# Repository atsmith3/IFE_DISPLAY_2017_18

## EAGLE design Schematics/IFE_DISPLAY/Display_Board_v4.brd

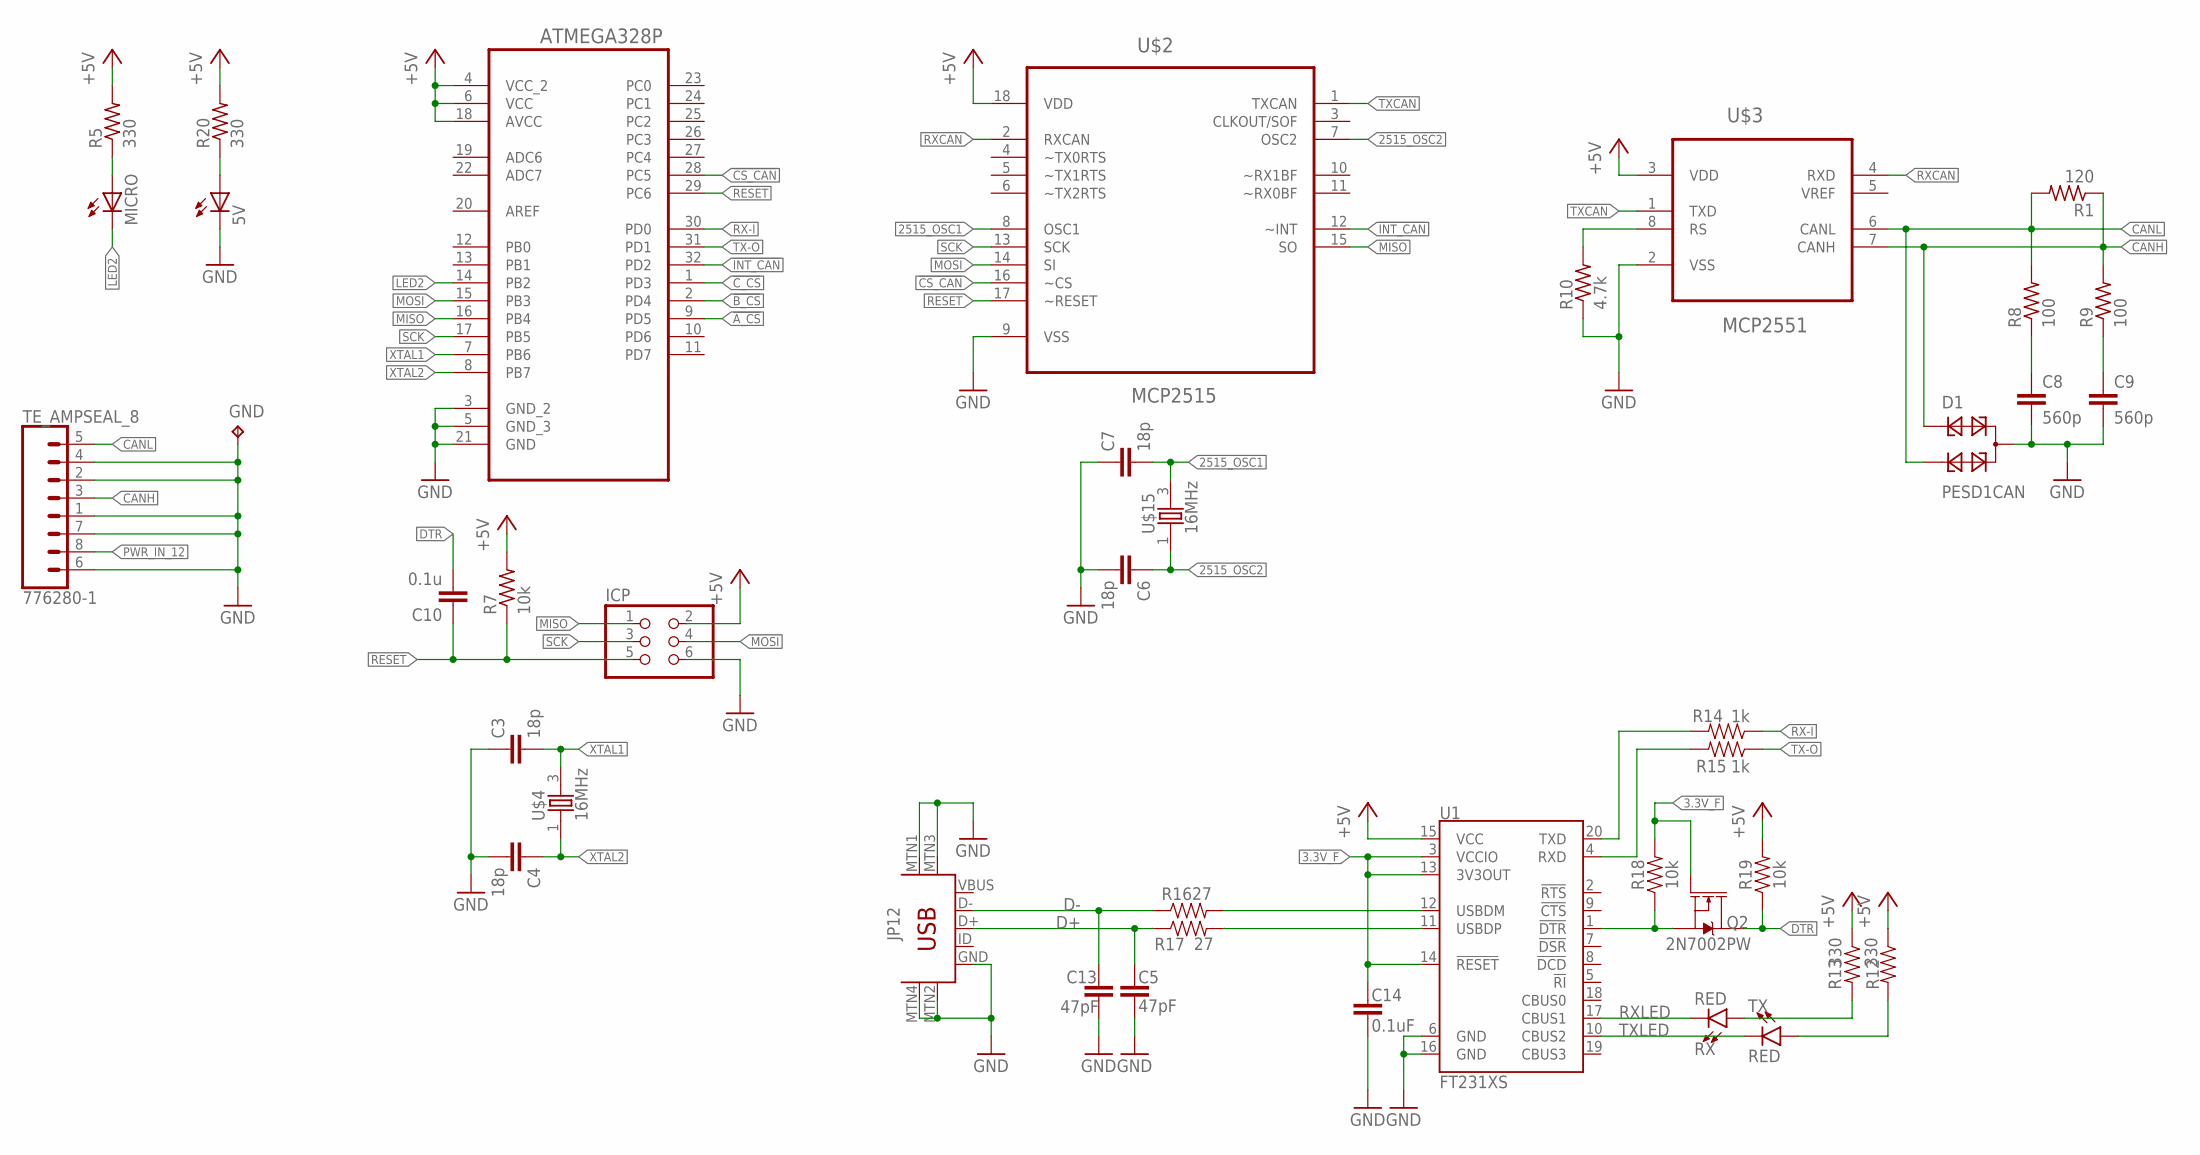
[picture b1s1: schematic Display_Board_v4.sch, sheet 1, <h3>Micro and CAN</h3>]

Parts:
5V: LEDCHIP-LED0805; CHIP-LED0805
ATMEGA328P: ATMEGA328P-AU; QFP80P900X900X120-32N
C3, C4, C6, C7: 18p; C0805K
C5, C13: 47pF; 0603
C8, C9: 560p; C0805K
C10: 0.1u; C0805K
C14: 0.1uF; 0603
D1: PESD1CAN; SOT23
GND: TPTP12SQ; TP12SQ
ICP: PINHD-2X3; 2X03
JP12: USB-MINIB-5PIN; USB-MINIB
MICRO: LEDCHIP-LED0805; CHIP-LED0805
Q2: 2N7002PW; SOT323
R1: 120; R0805
R5, R20: 330; R0805
R7: 10k; R0805
R8, R9: 100; R0805
R10: 4.7k; R0805
R12, R13: 330; 0603
R14, R15: 1k; 0603
R16, R17: 27; 0603
R18, R19: 10k; 0603
RX: RED; LED-1206
TE_AMPSEAL_8: 776280-1
TX: RED; LED-1206
U1: FT231XS; SSOP20_L
U$2: MCP2515; SOIC127P1034X264-18N
U$3: MCP2551; SOIC127P600X175-8N
U$4, U$15: 16MHz; CTS406

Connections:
3.3V_F: C14.1, Q2.1 (G), R18.2, U1.3 (VCCIO), U1.13 (3V3OUT), U1.14 (!RESET)
2515_OSC1: C7.2, U$2.8 (OSC1), U$15.3 (2)
2515_OSC2: C6.1, U$2.7 (OSC2), U$15.1
!A_CS: ATMEGA328P.9 (PD5); also elsewhere on the board
!B_CS: ATMEGA328P.2 (PD4); also elsewhere on the board
!CS_CAN: ATMEGA328P.28 (PC5), U$2.16 (~CS)
!C_CS: ATMEGA328P.1 (PD3); also elsewhere on the board
!INT_CAN: ATMEGA328P.32 (PD2), U$2.12 (~INT)
+5V: ATMEGA328P.4 (VCC_2), ATMEGA328P.6 (VCC), ATMEGA328P.18 (AVCC), ICP.2, R5.2, R7.2, R12.1, R13.1, R19.2, R20.2, U1.15 (VCC), U$2.18 (VDD), U$3.3 (VDD); also elsewhere on the board
CANH: D1.1, R1.1, R9.2, TE_AMPSEAL_8.3 (5), U$3.7 (CANH)
CANL: D1.2, R1.2, R8.2, TE_AMPSEAL_8.5 (8), U$3.6 (CANL)
D+: C5.1, JP12.D+, R17.1
D-: C13.1, JP12.D-, R16.1
DTR: C10.2, Q2.3 (D), R19.1
FTDI_DTR: Q2.2 (S), R18.1, U1.1 (!DTR)
GND: 5V.C, ATMEGA328P.3 (GND_2), ATMEGA328P.5 (GND_3), ATMEGA328P.21 (GND), C3.1, C4.2, C5.2, C6.2, C7.1, C8.2, C9.2, C13.2, C14.2, D1.3, GND.TP, ICP.6, JP12.GND, JP12.MTN1 (MTN2), JP12.MTN2 (MTN3), JP12.MTN3 (MTN1), JP12.MTN4, R10.1, TE_AMPSEAL_8.1 (4), TE_AMPSEAL_8.2 (6), TE_AMPSEAL_8.4 (7), TE_AMPSEAL_8.6 (1), TE_AMPSEAL_8.7 (3), U1.6 (GND), U1.16 (GND), U$2.9 (VSS), U$3.2 (VSS); also elsewhere on the board
LED2: ATMEGA328P.14 (PB2), MICRO.C
MISO: ATMEGA328P.16 (PB4), ICP.1, U$2.15 (SO); also elsewhere on the board
MOSI: ATMEGA328P.15 (PB3), ICP.4, U$2.14 (SI); also elsewhere on the board
unnamed: R12.2, TX.A
unnamed: R16.2, U1.12 (USBDM)
unnamed: MICRO.A, R5.1
unnamed: R17.2, U1.11 (USBDP)
unnamed: R10.2, U$3.8 (RS)
unnamed: C8.1, R8.1
unnamed: C9.1, R9.1
unnamed: R13.2, RX.A
unnamed: 5V.A, R20.1
PWR_IN_12: TE_AMPSEAL_8.8 (2); also elsewhere on the board
RESET: ATMEGA328P.29 (PC6), C10.1, ICP.5, R7.1, U$2.17 (~RESET)
RX-I: ATMEGA328P.30 (PD0), R14.1
RXCAN: U$2.2 (RXCAN), U$3.4 (RXD)
RXD1: R15.2, U1.4 (RXD)
RXLED: RX.C, U1.17 (CBUS1)
SCK: ATMEGA328P.17 (PB5), ICP.3, U$2.13 (SCK); also elsewhere on the board
TX-O: ATMEGA328P.31 (PD1), R15.1
TXCAN: U$2.1 (TXCAN), U$3.1 (TXD)
TXD1: R14.2, U1.20 (TXD)
TXLED: TX.C, U1.10 (CBUS2)
XTAL1: ATMEGA328P.7 (PB6), C3.2, U$4.3 (2)
XTAL2: ATMEGA328P.8 (PB7), C4.1, U$4.1

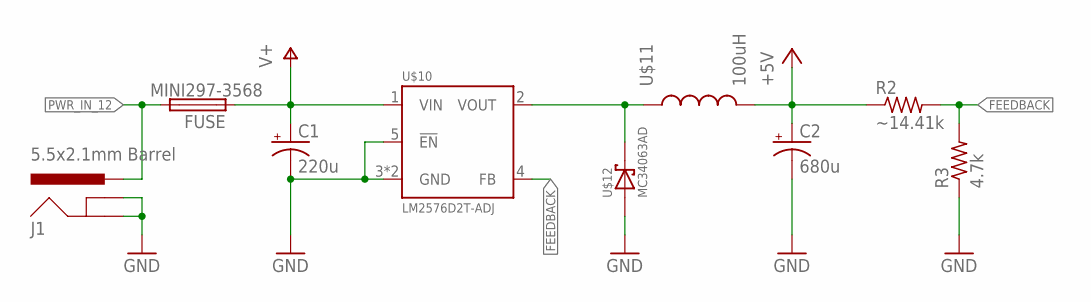
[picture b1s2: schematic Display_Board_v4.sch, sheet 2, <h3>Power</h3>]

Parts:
C1: 220u; UD-6,3X7,7_NICHICON
C2: 680u; UD-6,3X7,7_NICHICON
FUSE: MINI297-3568; 3568
J1: 5.5x2.1mm Barrel; POWER_JACK_SMD
R2: ~14.41k; R0603
R3: 4.7k; R0603
U$10: LM2576D2T-ADJ; TO263-5
U$11: 100uH; 12MM_12MM_INDUCTOR
U$12: MC34063AD; SMC

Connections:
+5V: C2.+, R2.1, U$11.P$2 (2); also elsewhere on the board
FEEDBACK: R2.2, R3.2, U$10.4 (FB)
GND: C1.-, C2.-, J1.GND (GNDBREAK), J1.P$4 (GND), R3.1, U$10.3 (GND), U$10.5 (!EN), U$10.6 (GND), U$12.A; also elsewhere on the board
unnamed: U$10.2 (VOUT), U$11.P$1 (1), U$12.C
PWR_IN_12: FUSE.P$2 (2), FUSE.P$3 (2), J1.VIN0 (PWR); also elsewhere on the board
V+: C1.+, FUSE.P$1 (1), FUSE.P$4 (1), U$10.1 (VIN)

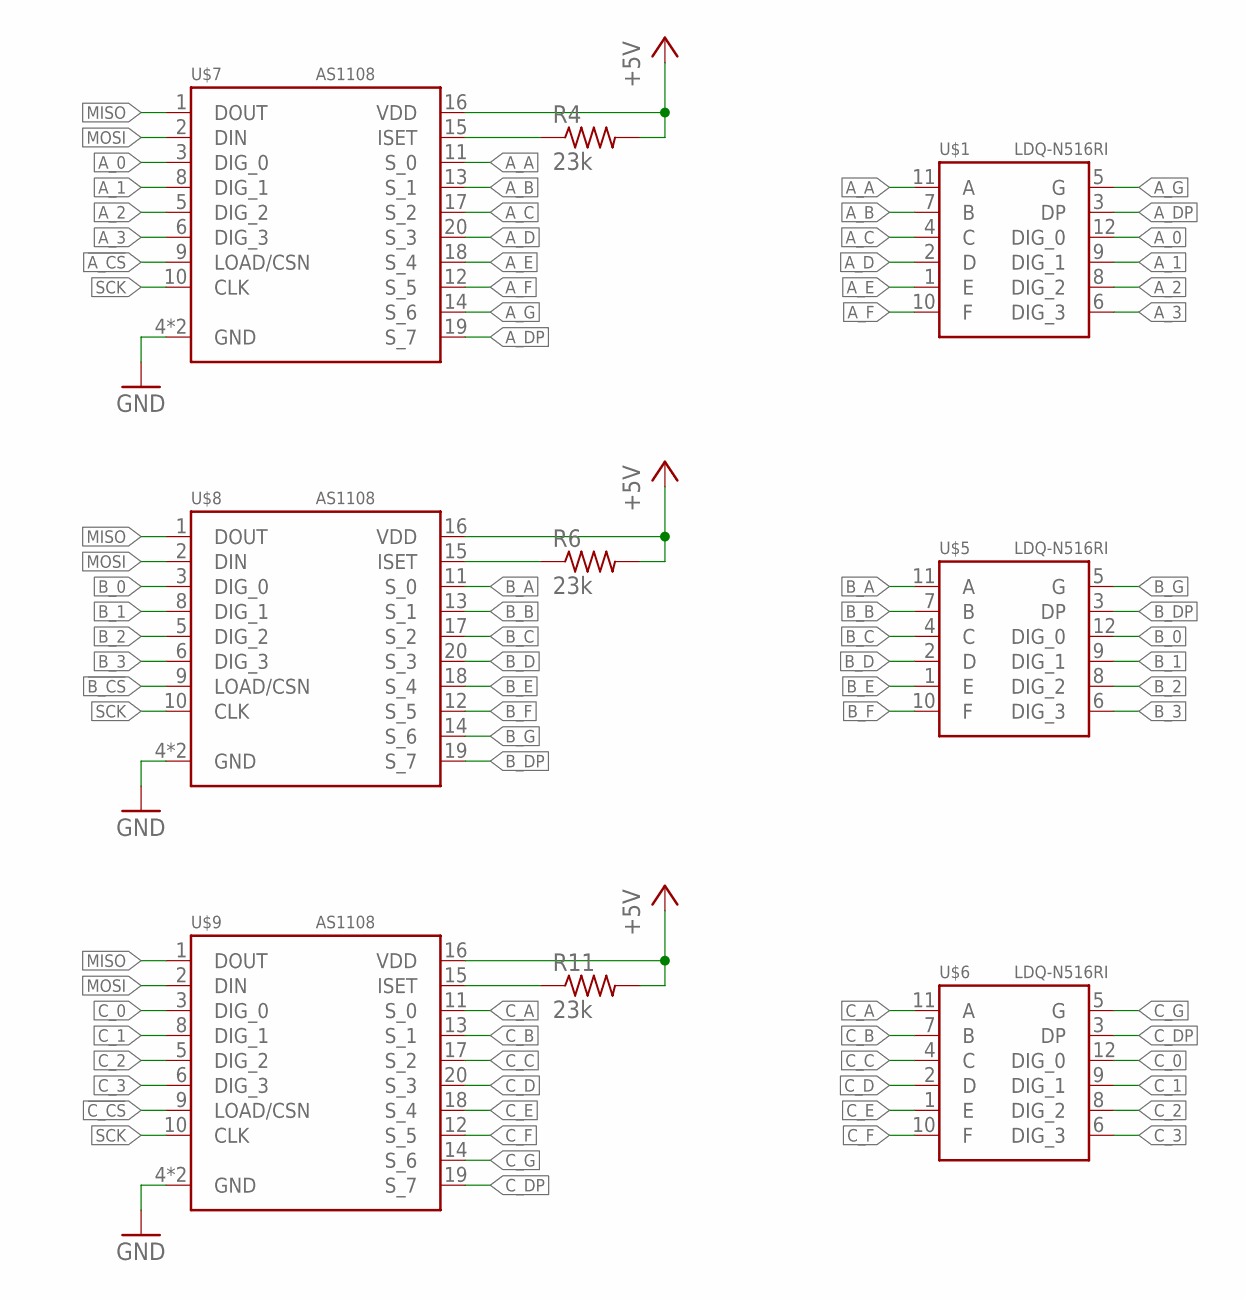
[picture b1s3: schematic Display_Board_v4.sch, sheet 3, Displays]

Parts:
R4, R6, R11: 23k; R0603
U$1, U$5, U$6: LDQ-N516RI; 4_DIGIT_7_SEGMENT_DISPLAY_0.56"
U$7, U$8, U$9: AS1108; SO20L

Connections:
!A_CS: U$7.9 (LOAD/CSN); also elsewhere on the board
!B_CS: U$8.9 (LOAD/CSN); also elsewhere on the board
!C_CS: U$9.9 (LOAD/CSN); also elsewhere on the board
+5V: R4.2, R6.2, R11.2, U$7.16 (VDD), U$8.16 (VDD), U$9.16 (VDD); also elsewhere on the board
A_0: U$1.12 (DIG_0), U$7.3 (DIG_0)
A_1: U$1.9 (DIG_1), U$7.8 (DIG_1)
A_2: U$1.8 (DIG_2), U$7.5 (DIG_2)
A_3: U$1.6 (DIG_3), U$7.6 (DIG_3)
A_A: U$1.11 (A), U$7.11 (S_0)
A_B: U$1.7 (B), U$7.13 (S_1)
A_C: U$1.4 (C), U$7.17 (S_2)
A_D: U$1.2 (D), U$7.20 (S_3)
A_DP: U$1.3 (DP), U$7.19 (S_7)
A_E: U$1.1 (E), U$7.18 (S_4)
A_F: U$1.10 (F), U$7.12 (S_5)
A_G: U$1.5 (G), U$7.14 (S_6)
B_0: U$5.12 (DIG_0), U$8.3 (DIG_0)
B_1: U$5.9 (DIG_1), U$8.8 (DIG_1)
B_2: U$5.8 (DIG_2), U$8.5 (DIG_2)
B_3: U$5.6 (DIG_3), U$8.6 (DIG_3)
B_A: U$5.11 (A), U$8.11 (S_0)
B_B: U$5.7 (B), U$8.13 (S_1)
B_C: U$5.4 (C), U$8.17 (S_2)
B_D: U$5.2 (D), U$8.20 (S_3)
B_DP: U$5.3 (DP), U$8.19 (S_7)
B_E: U$5.1 (E), U$8.18 (S_4)
B_F: U$5.10 (F), U$8.12 (S_5)
B_G: U$5.5 (G), U$8.14 (S_6)
C_0: U$6.12 (DIG_0), U$9.3 (DIG_0)
C_1: U$6.9 (DIG_1), U$9.8 (DIG_1)
C_2: U$6.8 (DIG_2), U$9.5 (DIG_2)
C_3: U$6.6 (DIG_3), U$9.6 (DIG_3)
C_A: U$6.11 (A), U$9.11 (S_0)
C_B: U$6.7 (B), U$9.13 (S_1)
C_C: U$6.4 (C), U$9.17 (S_2)
C_D: U$6.2 (D), U$9.20 (S_3)
C_DP: U$6.3 (DP), U$9.19 (S_7)
C_E: U$6.1 (E), U$9.18 (S_4)
C_F: U$6.10 (F), U$9.12 (S_5)
C_G: U$6.5 (G), U$9.14 (S_6)
GND: U$7.4 (GND), U$7.7 (GND), U$8.4 (GND), U$8.7 (GND), U$9.4 (GND), U$9.7 (GND); also elsewhere on the board
MISO: U$7.1 (DOUT), U$8.1 (DOUT), U$9.1 (DOUT); also elsewhere on the board
MOSI: U$7.2 (DIN), U$8.2 (DIN), U$9.2 (DIN); also elsewhere on the board
unnamed: R6.1, U$8.15 (ISET)
unnamed: R11.1, U$9.15 (ISET)
unnamed: R4.1, U$7.15 (ISET)
SCK: U$7.10 (CLK), U$8.10 (CLK), U$9.10 (CLK); also elsewhere on the board

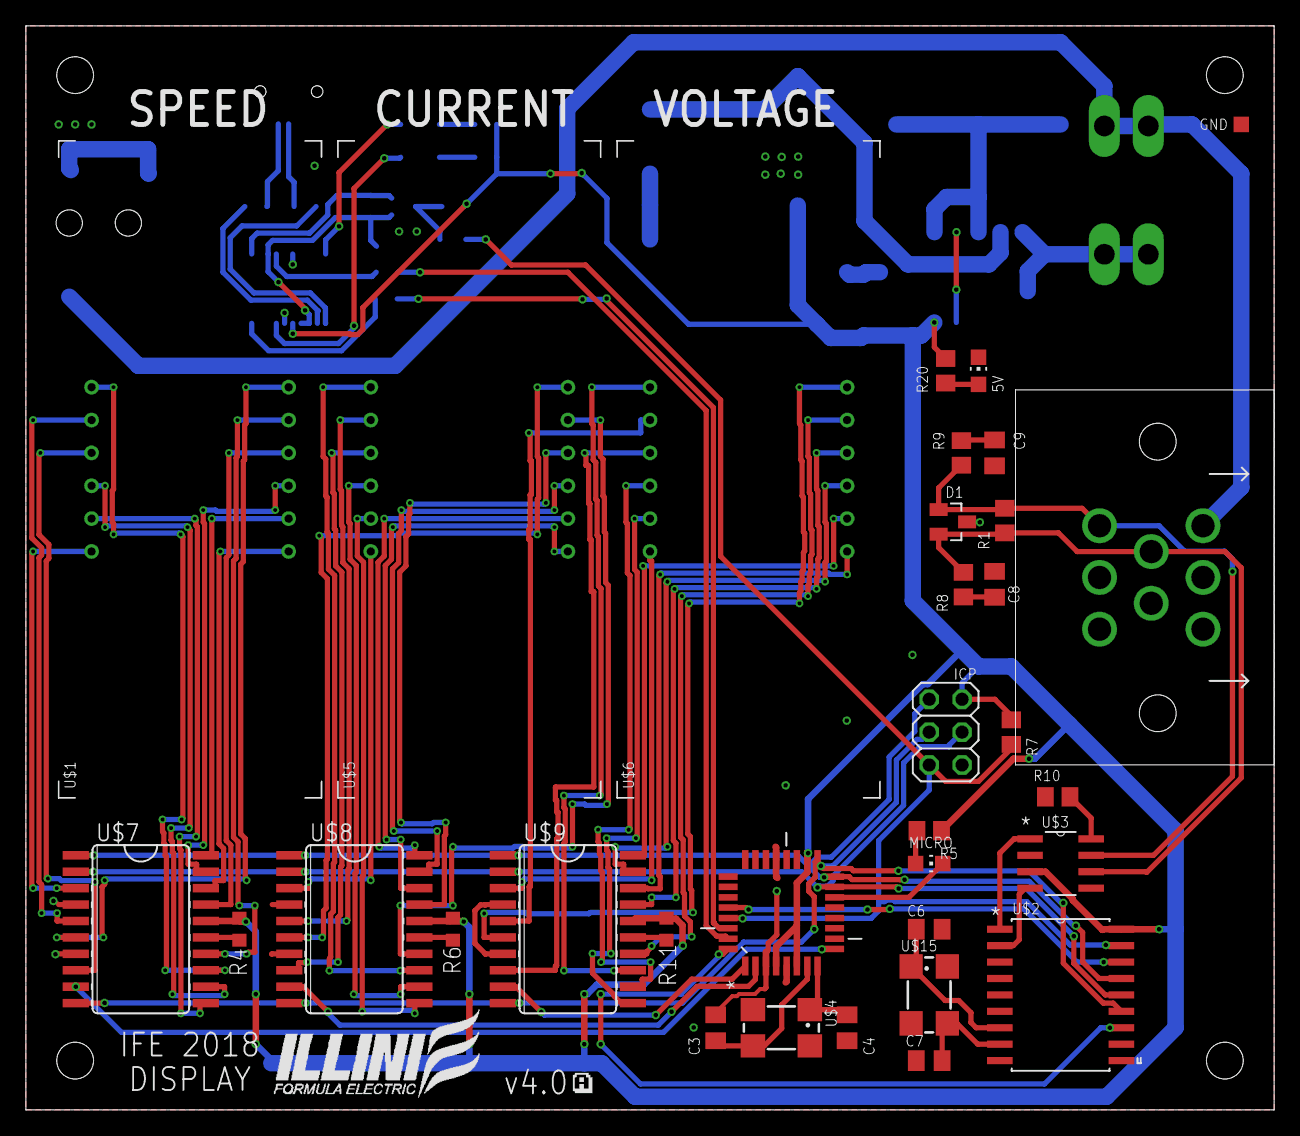
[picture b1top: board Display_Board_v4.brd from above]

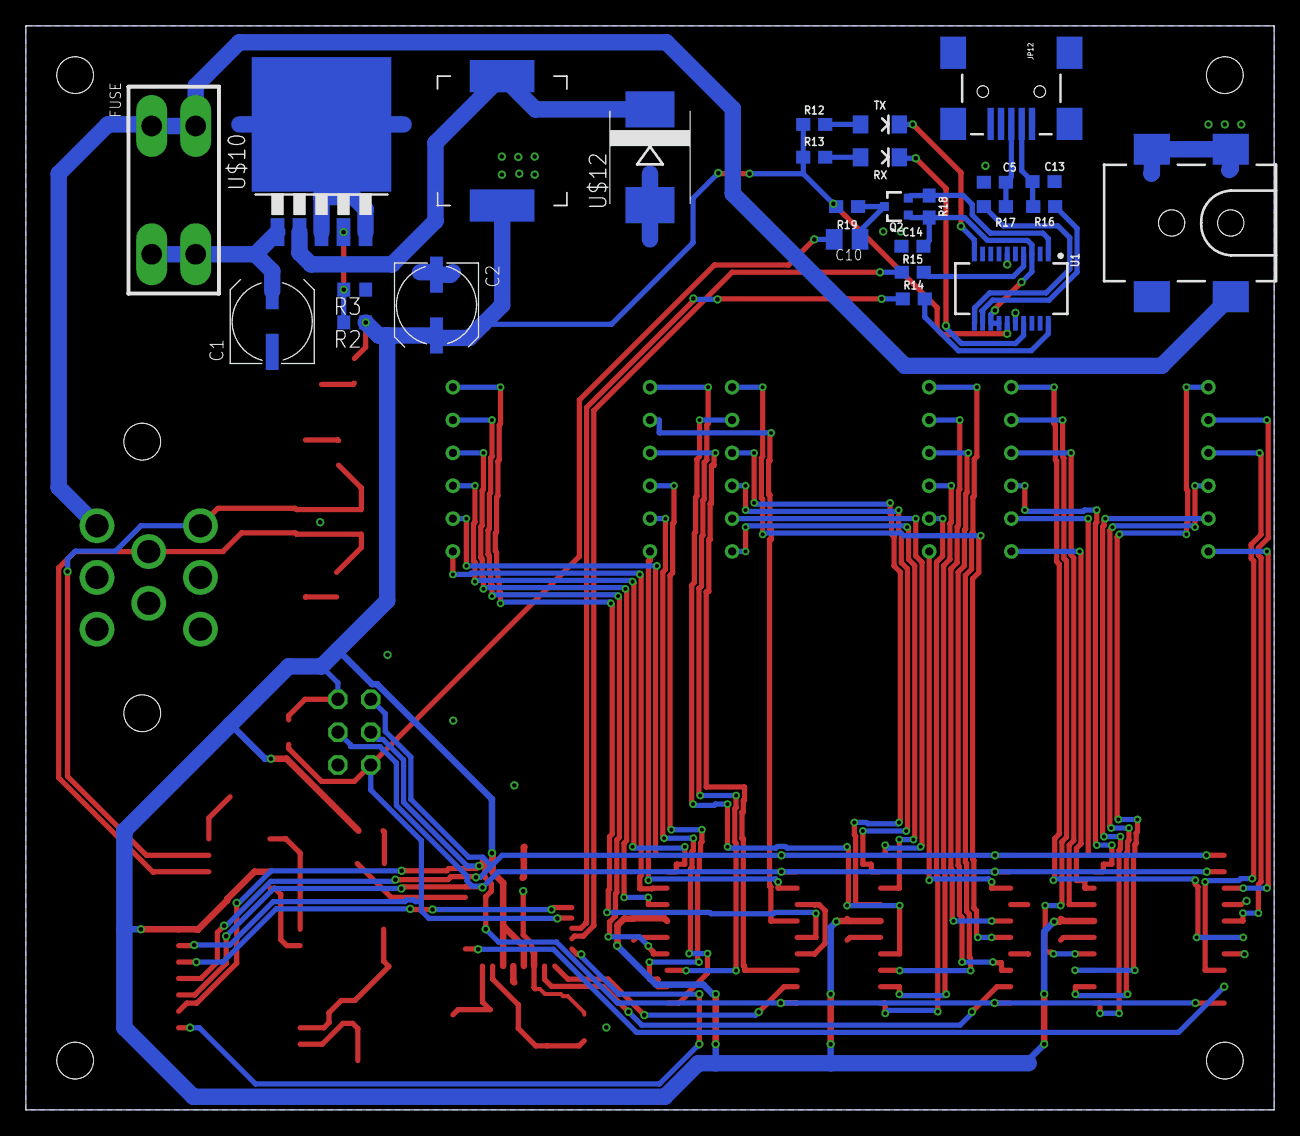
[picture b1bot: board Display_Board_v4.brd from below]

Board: 2 copper layers, 96.5 x 83.8 mm, 59 parts (26 on the bottom side), 83 nets.

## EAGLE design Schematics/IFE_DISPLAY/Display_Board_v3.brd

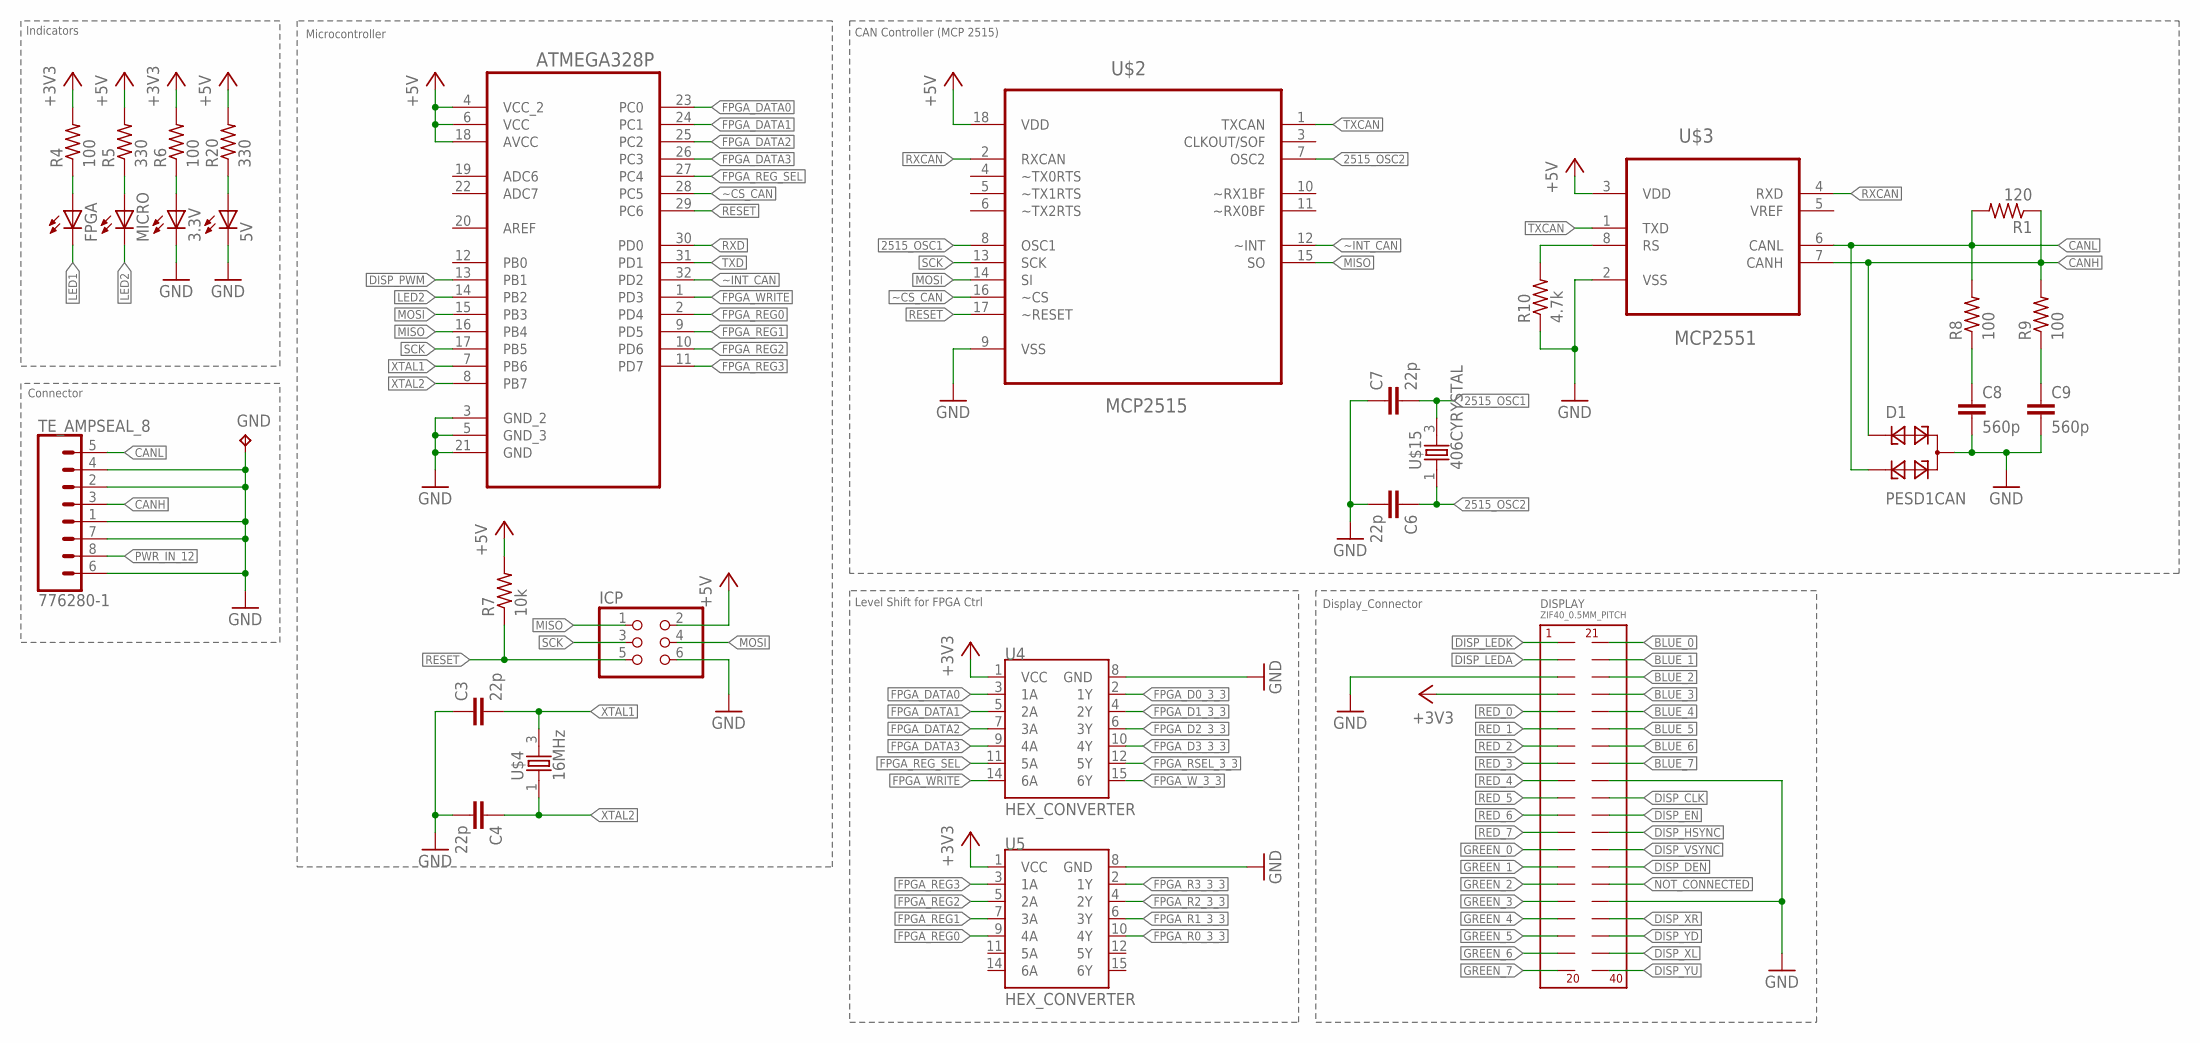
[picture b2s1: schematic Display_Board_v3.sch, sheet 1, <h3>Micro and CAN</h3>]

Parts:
3.3V, 5V: LEDCHIP-LED0805; CHIP-LED0805
ATMEGA328P: ATMEGA328P-AU; QFP80P900X900X120-32N
C3, C4, C6, C7: 22p; C0805K
C8, C9: 560p; C0805K
D1: PESD1CAN; SOT23
DISPLAY: ZIF40_0.5MM_PITCH; ZIF40
FPGA: LEDCHIP-LED0805; CHIP-LED0805
GND: TPTP12SQ; TP12SQ
ICP: PINHD-2X3; 2X03
MICRO: LEDCHIP-LED0805; CHIP-LED0805
R1: 120; R0805
R4, R6, R8, R9: 100; R0805
R5, R20: 330; R0805
R7: 10k; R0805
R10: 4.7k; R0805
TE_AMPSEAL_8: 776280-1
U4, U5: HEX_CONVERTER; SO016
U$2: MCP2515; SOIC127P1034X264-18N
U$3: MCP2551; SOIC127P600X175-8N
U$4: 16MHz; CTS406
U$15: 406CYRYSTAL; CTS406

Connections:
2515_OSC1: C7.2, U$2.8 (OSC1), U$15.3 (2)
2515_OSC2: C6.1, U$2.7 (OSC2), U$15.1
+3V3: DISPLAY.P$4, R4.2, R6.2, U4.1 (VCC), U5.1 (VCC); also elsewhere on the board
+5V: ATMEGA328P.4 (VCC_2), ATMEGA328P.6 (VCC), ATMEGA328P.18 (AVCC), ICP.2, R5.2, R7.2, R20.2, U$2.18 (VDD), U$3.3 (VDD); also elsewhere on the board
BLUE_0: DISPLAY.P$21; also elsewhere on the board
BLUE_1: DISPLAY.P$22; also elsewhere on the board
BLUE_2: DISPLAY.P$23; also elsewhere on the board
BLUE_3: DISPLAY.P$24; also elsewhere on the board
BLUE_4: DISPLAY.P$25; also elsewhere on the board
BLUE_5: DISPLAY.P$26; also elsewhere on the board
BLUE_6: DISPLAY.P$27; also elsewhere on the board
BLUE_7: DISPLAY.P$28; also elsewhere on the board
CANH: D1.1, R1.1, R9.2, TE_AMPSEAL_8.3 (5), U$3.7 (CANH)
CANL: D1.2, R1.2, R8.2, TE_AMPSEAL_8.5 (8), U$3.6 (CANL)
DISP_CLK: DISPLAY.P$30; also elsewhere on the board
DISP_DEN: DISPLAY.P$34; also elsewhere on the board
DISP_EN: DISPLAY.P$31; also elsewhere on the board
DISP_HSYNC: DISPLAY.P$32; also elsewhere on the board
DISP_LEDA: DISPLAY.P$2; also elsewhere on the board
DISP_LEDK: DISPLAY.P$1; also elsewhere on the board
DISP_PWM: ATMEGA328P.13 (PB1); also elsewhere on the board
DISP_VSYNC: DISPLAY.P$33; also elsewhere on the board
DISP_XL: DISPLAY.P$39
DISP_XR: DISPLAY.P$37
DISP_YD: DISPLAY.P$38
DISP_YU: DISPLAY.P$40
FPGA_D0_3_3: U4.2 (1Y); also elsewhere on the board
FPGA_D1_3_3: U4.4 (2Y); also elsewhere on the board
FPGA_D2_3_3: U4.6 (3Y); also elsewhere on the board
FPGA_D3_3_3: U4.10 (4Y); also elsewhere on the board
FPGA_DATA0: ATMEGA328P.23 (PC0), U4.3 (1A)
FPGA_DATA1: ATMEGA328P.24 (PC1), U4.5 (2A)
FPGA_DATA2: ATMEGA328P.25 (PC2), U4.7 (3A)
FPGA_DATA3: ATMEGA328P.26 (PC3), U4.9 (4A)
FPGA_R0_3_3: U5.10 (4Y); also elsewhere on the board
FPGA_R1_3_3: U5.6 (3Y); also elsewhere on the board
FPGA_R2_3_3: U5.4 (2Y); also elsewhere on the board
FPGA_R3_3_3: U5.2 (1Y); also elsewhere on the board
FPGA_REG0: ATMEGA328P.2 (PD4), U5.9 (4A)
FPGA_REG1: ATMEGA328P.9 (PD5), U5.7 (3A)
FPGA_REG2: ATMEGA328P.10 (PD6), U5.5 (2A)
FPGA_REG3: ATMEGA328P.11 (PD7), U5.3 (1A)
FPGA_REG_SEL: ATMEGA328P.27 (PC4), U4.11 (5A)
FPGA_RSEL_3_3: U4.12 (5Y); also elsewhere on the board
FPGA_WRITE: ATMEGA328P.1 (PD3), U4.14 (6A)
FPGA_W_3_3: U4.15 (6Y); also elsewhere on the board
GND: 3.3V.C, 5V.C, ATMEGA328P.3 (GND_2), ATMEGA328P.5 (GND_3), ATMEGA328P.21 (GND), C3.1, C4.2, C6.2, C7.1, C8.2, C9.2, D1.3, DISPLAY.P$3, DISPLAY.P$29, DISPLAY.P$36, GND.TP, ICP.6, R10.1, TE_AMPSEAL_8.1 (4), TE_AMPSEAL_8.2 (6), TE_AMPSEAL_8.4 (7), TE_AMPSEAL_8.6 (1), TE_AMPSEAL_8.7 (3), U4.8 (GND), U5.8 (GND), U$2.9 (VSS), U$3.2 (VSS); also elsewhere on the board
GREEN_0: DISPLAY.P$13; also elsewhere on the board
GREEN_1: DISPLAY.P$14; also elsewhere on the board
GREEN_2: DISPLAY.P$15; also elsewhere on the board
GREEN_3: DISPLAY.P$16; also elsewhere on the board
GREEN_4: DISPLAY.P$17; also elsewhere on the board
GREEN_5: DISPLAY.P$18; also elsewhere on the board
GREEN_6: DISPLAY.P$19; also elsewhere on the board
GREEN_7: DISPLAY.P$20; also elsewhere on the board
LED1: FPGA.C; also elsewhere on the board
LED2: ATMEGA328P.14 (PB2), MICRO.C
MISO: ATMEGA328P.16 (PB4), ICP.1, U$2.15 (SO)
MOSI: ATMEGA328P.15 (PB3), ICP.4, U$2.14 (SI)
unnamed: FPGA.A, R4.1
unnamed: MICRO.A, R5.1
unnamed: 3.3V.A, R6.1
unnamed: R10.2, U$3.8 (RS)
unnamed: C8.1, R8.1
unnamed: C9.1, R9.1
unnamed: 5V.A, R20.1
NOT_CONNECTED: DISPLAY.P$35
PWR_IN_12: TE_AMPSEAL_8.8 (2); also elsewhere on the board
RED_0: DISPLAY.P$5; also elsewhere on the board
RED_1: DISPLAY.P$6; also elsewhere on the board
RED_2: DISPLAY.P$7; also elsewhere on the board
RED_3: DISPLAY.P$8; also elsewhere on the board
RED_4: DISPLAY.P$9; also elsewhere on the board
RED_5: DISPLAY.P$10; also elsewhere on the board
RED_6: DISPLAY.P$11; also elsewhere on the board
RED_7: DISPLAY.P$12; also elsewhere on the board
RESET: ATMEGA328P.29 (PC6), ICP.5, R7.1, U$2.17 (~RESET)
RXCAN: U$2.2 (RXCAN), U$3.4 (RXD)
RXD: ATMEGA328P.30 (PD0)
SCK: ATMEGA328P.17 (PB5), ICP.3, U$2.13 (SCK)
TXCAN: U$2.1 (TXCAN), U$3.1 (TXD)
TXD: ATMEGA328P.31 (PD1)
XTAL1: ATMEGA328P.7 (PB6), C3.2, U$4.3 (2)
XTAL2: ATMEGA328P.8 (PB7), C4.1, U$4.1
~CS_CAN: ATMEGA328P.28 (PC5), U$2.16 (~CS)
~INT_CAN: ATMEGA328P.32 (PD2), U$2.12 (~INT)

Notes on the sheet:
Microcontroller
CAN Controller (MCP 2515)
Indicators
Level Shift for FPGA Ctrl
Connector
Display_Connector

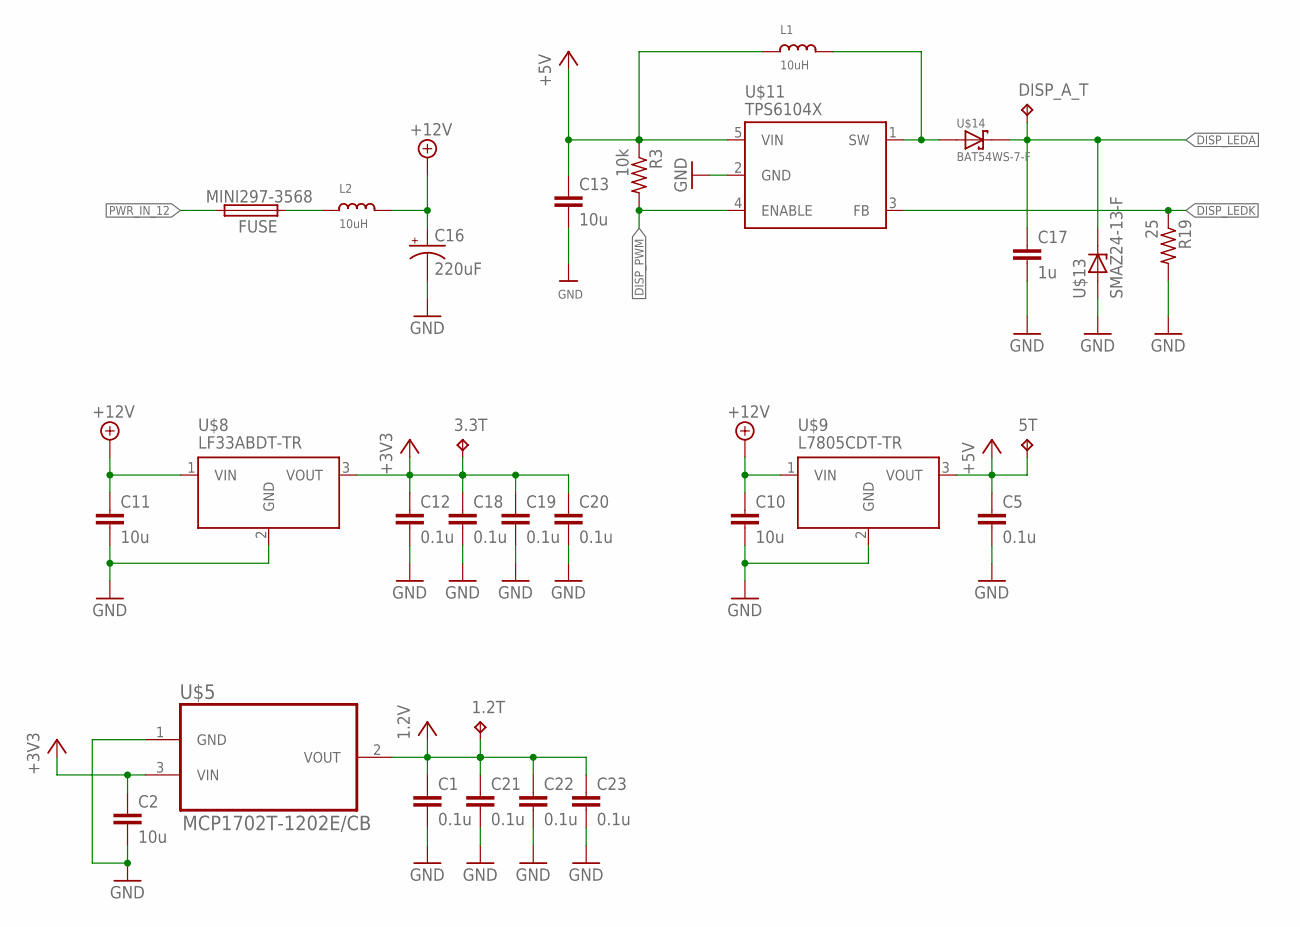
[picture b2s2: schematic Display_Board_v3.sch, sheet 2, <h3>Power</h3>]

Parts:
1.2T, 3.3T, 5T: TPTP12SQ; TP12SQ
C1, C5, C12, C18, C19, C20, C21, C22, C23: 0.1u; C0805K
C2, C10, C11, C13: 10u; C0805K
C16: 220uF; UD-6,3X7,7_NICHICON
C17: 1u; C0805K
DISP_A_T: TPTP12SQ; TP12SQ
FUSE: MINI297-3568; 3568
L1, L2: 10uH; INDUCTOR_5X5MM_NR5040_NOTHERMALS
R3: 10k; R0805
R19: 25; R0805
U$5: MCP1702T-1202E/CB; SOT95P300X145-3N
U$8: LF33ABDT-TR; DPACK
U$9: L7805CDT-TR; DPACK
U$11: TPS6104X; SOT23-5L
U$13: SMAZ24-13-F; SMA_DIODE
U$14: BAT54WS-7-F; SOD323

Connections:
+3V3: 3.3T.TP, C2.1, C12.1, C18.1, C19.1, C20.1, U$5.3 (VIN), U$8.3 (VOUT); also elsewhere on the board
+5V: 5T.TP, C5.1, C13.1, L1.P$1 (1), R3.1, U$9.3 (VOUT), U$11.5 (VIN); also elsewhere on the board
+12V: C10.1, C11.1, C16.+, L2.P$2 (2), U$8.1 (VIN), U$9.1 (VIN)
DISP_LEDA: C17.1, DISP_A_T.TP, U$13.C, U$14.1 (C); also elsewhere on the board
DISP_LEDK: R19.1, U$11.3 (FB); also elsewhere on the board
DISP_PWM: R3.2, U$11.4 (ENABLE); also elsewhere on the board
GND: C1.2, C2.2, C5.2, C10.2, C11.2, C12.2, C13.2, C16.-, C17.2, C18.2, C19.2, C20.2, C21.2, C22.2, C23.2, R19.2, U$5.1 (GND), U$8.2 (GND), U$9.2 (GND), U$11.2 (GND), U$13.A; also elsewhere on the board
unnamed: FUSE.P$1 (1), FUSE.P$4 (1), L2.P$1 (1)
unnamed: L1.P$2 (2), U$11.1 (SW), U$14.2 (A)
PWR_IN_12: FUSE.P$2 (2), FUSE.P$3 (2); also elsewhere on the board
VCC: 1.2T.TP, C1.1, C21.1, C22.1, C23.1, U$5.2 (VOUT); also elsewhere on the board

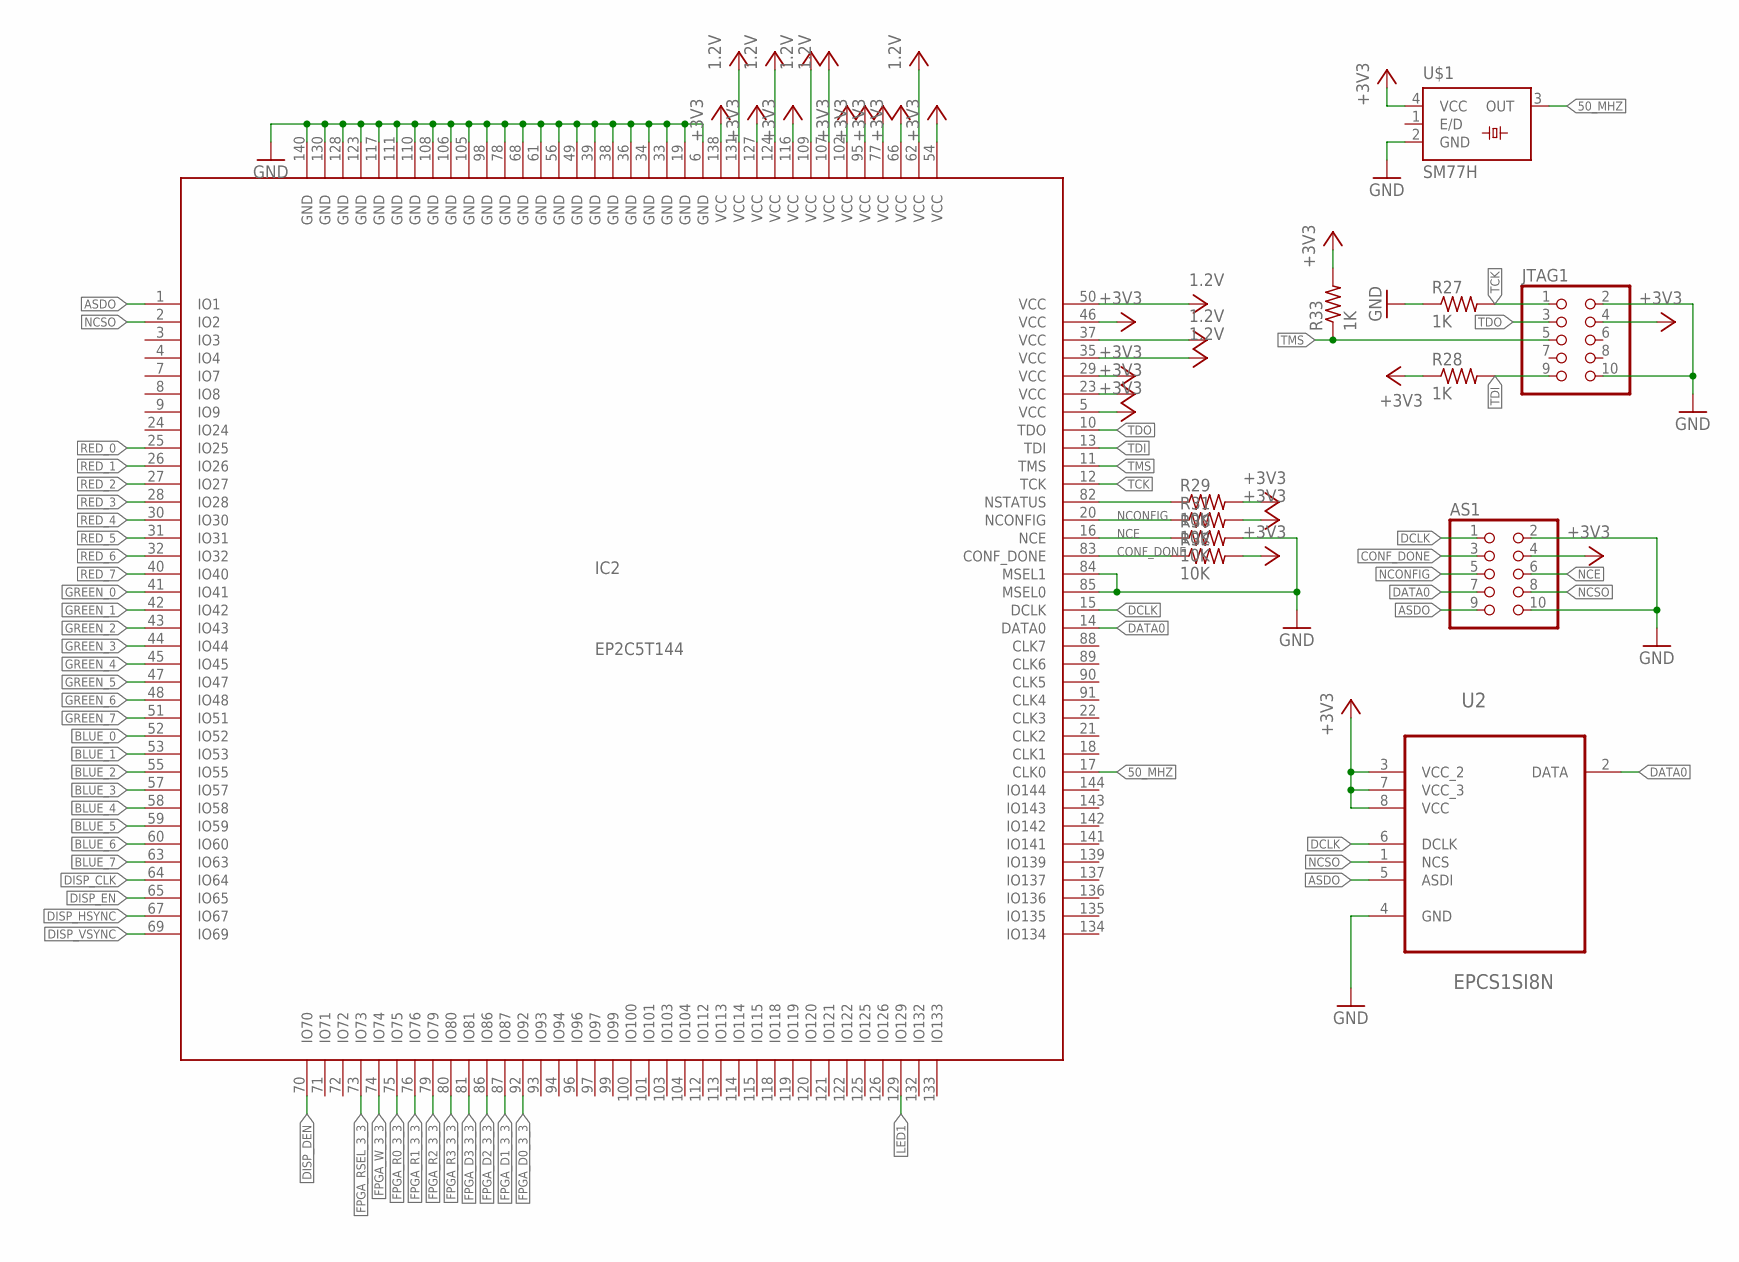
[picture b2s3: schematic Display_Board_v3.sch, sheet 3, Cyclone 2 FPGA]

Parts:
AS1: PINHD-2X5; 2X05
IC2: EP2C5T144; TQFP144
JTAG1: PINHD-2X5; 2X05
R27, R28, R33: 1K; R0805
R29, R30, R31, R32: 10K; R0805
U2: EPCS1SI8N; SOIC127P600X175-8N
U$1: SM77H

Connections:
50_MHZ: IC2.17 (CLK0), U$1.3 (OUT)
+3V3: AS1.4, IC2.5 (VCC), IC2.23 (VCC), IC2.29 (VCC), IC2.46 (VCC), IC2.54 (VCC), IC2.66 (VCC), IC2.77 (VCC), IC2.95 (VCC), IC2.102 (VCC), IC2.116 (VCC), IC2.127 (VCC), IC2.138 (VCC), JTAG1.4, R28.1, R29.2, R31.2, R32.2, R33.2, U2.3 (VCC_2), U2.7 (VCC_3), U2.8 (VCC), U$1.4 (VCC); also elsewhere on the board
ASDO: AS1.9, IC2.1 (IO1), U2.5 (ASDI)
BLUE_0: IC2.52 (IO52); also elsewhere on the board
BLUE_1: IC2.53 (IO53); also elsewhere on the board
BLUE_2: IC2.55 (IO55); also elsewhere on the board
BLUE_3: IC2.57 (IO57); also elsewhere on the board
BLUE_4: IC2.58 (IO58); also elsewhere on the board
BLUE_5: IC2.59 (IO59); also elsewhere on the board
BLUE_6: IC2.60 (IO60); also elsewhere on the board
BLUE_7: IC2.63 (IO63); also elsewhere on the board
CONF_DONE: AS1.3, IC2.83 (CONF_DONE), R32.1
DATA0: AS1.7, IC2.14 (DATA0), U2.2 (DATA)
DCLK: AS1.1, IC2.15 (DCLK), U2.6 (DCLK)
DISP_CLK: IC2.64 (IO64); also elsewhere on the board
DISP_DEN: IC2.70 (IO70); also elsewhere on the board
DISP_EN: IC2.65 (IO65); also elsewhere on the board
DISP_HSYNC: IC2.67 (IO67); also elsewhere on the board
DISP_VSYNC: IC2.69 (IO69); also elsewhere on the board
FPGA_D0_3_3: IC2.92 (IO92); also elsewhere on the board
FPGA_D1_3_3: IC2.87 (IO87); also elsewhere on the board
FPGA_D2_3_3: IC2.86 (IO86); also elsewhere on the board
FPGA_D3_3_3: IC2.81 (IO81); also elsewhere on the board
FPGA_R0_3_3: IC2.75 (IO75); also elsewhere on the board
FPGA_R1_3_3: IC2.76 (IO76); also elsewhere on the board
FPGA_R2_3_3: IC2.79 (IO79); also elsewhere on the board
FPGA_R3_3_3: IC2.80 (IO80); also elsewhere on the board
FPGA_RSEL_3_3: IC2.73 (IO73); also elsewhere on the board
FPGA_W_3_3: IC2.74 (IO74); also elsewhere on the board
GND: AS1.2, AS1.10, IC2.6 (GND), IC2.19 (GND), IC2.33 (GND), IC2.34 (GND), IC2.36 (GND), IC2.38 (GND), IC2.39 (GND), IC2.49 (GND), IC2.56 (GND), IC2.61 (GND), IC2.68 (GND), IC2.78 (GND), IC2.84 (MSEL1), IC2.85 (MSEL0), IC2.98 (GND), IC2.105 (GND), IC2.106 (GND), IC2.108 (GND), IC2.110 (GND), IC2.111 (GND), IC2.117 (GND), IC2.123 (GND), IC2.128 (GND), IC2.130 (GND), IC2.140 (GND), JTAG1.2, JTAG1.10, R27.1, R30.2, U2.4 (GND), U$1.2 (GND); also elsewhere on the board
GREEN_0: IC2.41 (IO41); also elsewhere on the board
GREEN_1: IC2.42 (IO42); also elsewhere on the board
GREEN_2: IC2.43 (IO43); also elsewhere on the board
GREEN_3: IC2.44 (IO44); also elsewhere on the board
GREEN_4: IC2.45 (IO45); also elsewhere on the board
GREEN_5: IC2.47 (IO47); also elsewhere on the board
GREEN_6: IC2.48 (IO48); also elsewhere on the board
GREEN_7: IC2.51 (IO51); also elsewhere on the board
LED1: IC2.129 (IO129); also elsewhere on the board
unnamed: IC2.82 (NSTATUS), R29.1
NCE: AS1.6, IC2.16 (NCE), R30.1
NCONFIG: AS1.5, IC2.20 (NCONFIG), R31.1
NCSO: AS1.8, IC2.2 (IO2), U2.1 (NCS)
RED_0: IC2.25 (IO25); also elsewhere on the board
RED_1: IC2.26 (IO26); also elsewhere on the board
RED_2: IC2.27 (IO27); also elsewhere on the board
RED_3: IC2.28 (IO28); also elsewhere on the board
RED_4: IC2.30 (IO30); also elsewhere on the board
RED_5: IC2.31 (IO31); also elsewhere on the board
RED_6: IC2.32 (IO32); also elsewhere on the board
RED_7: IC2.40 (IO40); also elsewhere on the board
TCK: IC2.12 (TCK), JTAG1.1, R27.2
TDI: IC2.13 (TDI), JTAG1.9, R28.2
TDO: IC2.10 (TDO), JTAG1.3
TMS: IC2.11 (TMS), JTAG1.5, R33.1
VCC: IC2.35 (VCC), IC2.37 (VCC), IC2.50 (VCC), IC2.62 (VCC), IC2.107 (VCC), IC2.109 (VCC), IC2.124 (VCC), IC2.131 (VCC); also elsewhere on the board

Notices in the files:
parts and their libraries:
SparkFun-DigitalIC: Licensing: Creative Commons ShareAlike 4.0 International - https://creativecommons.org/licenses/by-sa/4.0
SparkFun-Capacitors: Licensing: CC v3.0 Share-Alike You are welcome to use this library for commercial purposes.
